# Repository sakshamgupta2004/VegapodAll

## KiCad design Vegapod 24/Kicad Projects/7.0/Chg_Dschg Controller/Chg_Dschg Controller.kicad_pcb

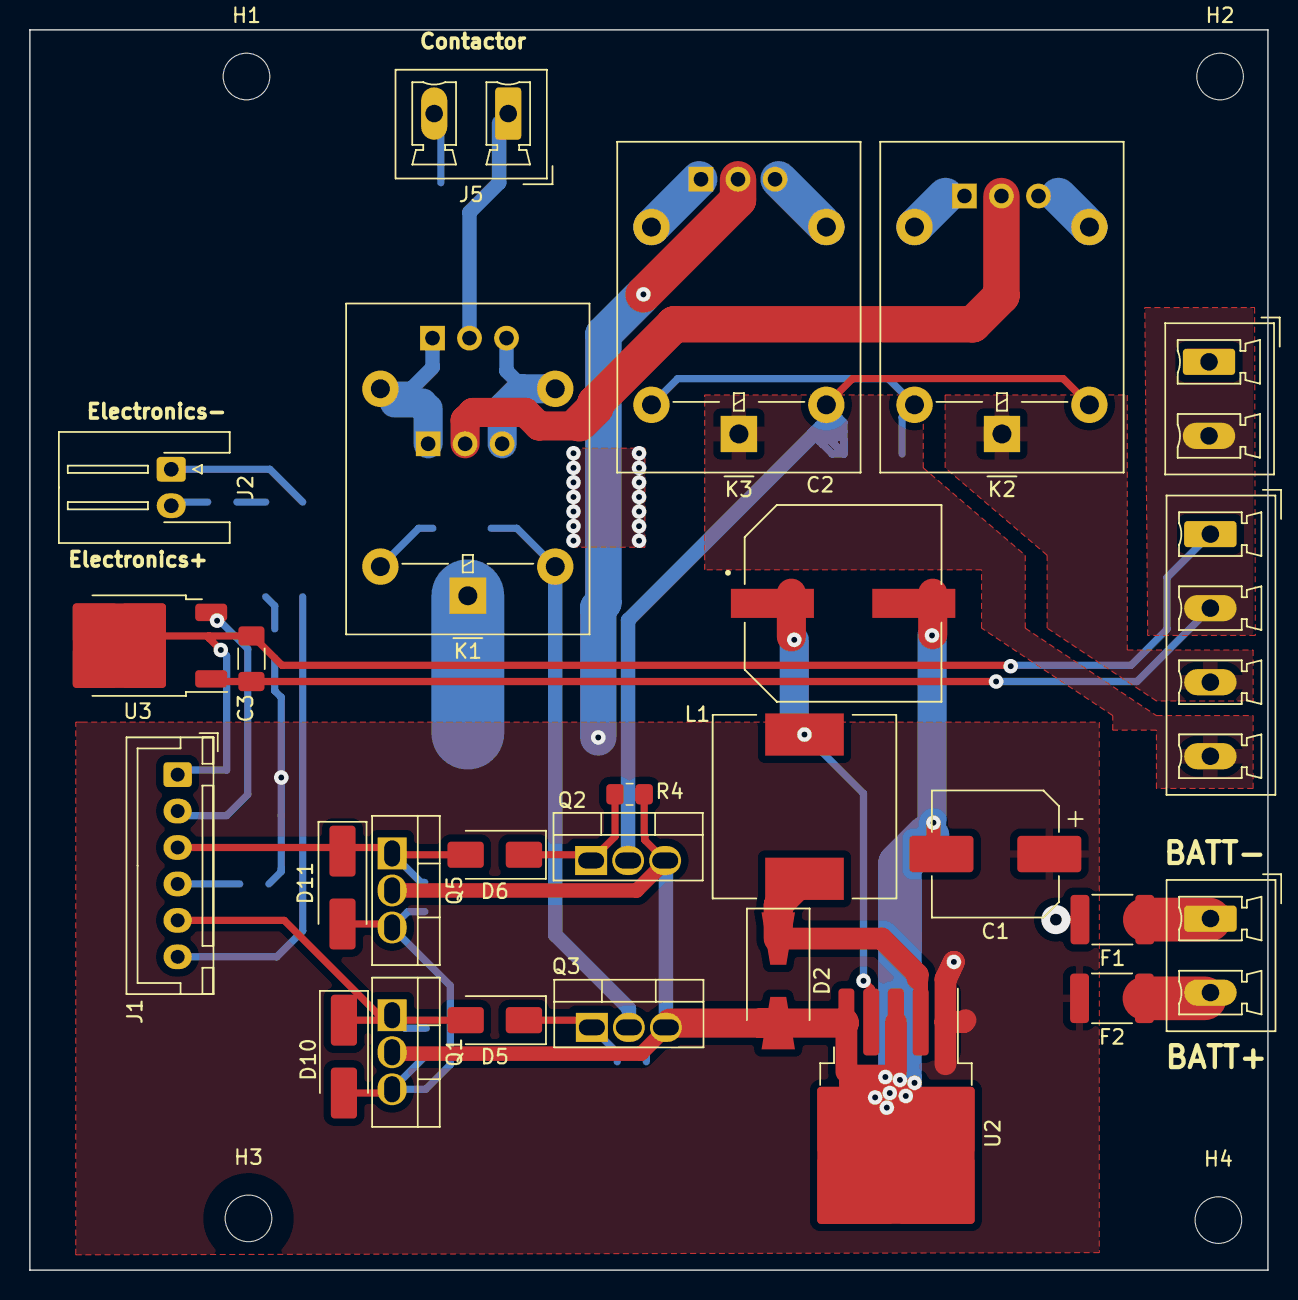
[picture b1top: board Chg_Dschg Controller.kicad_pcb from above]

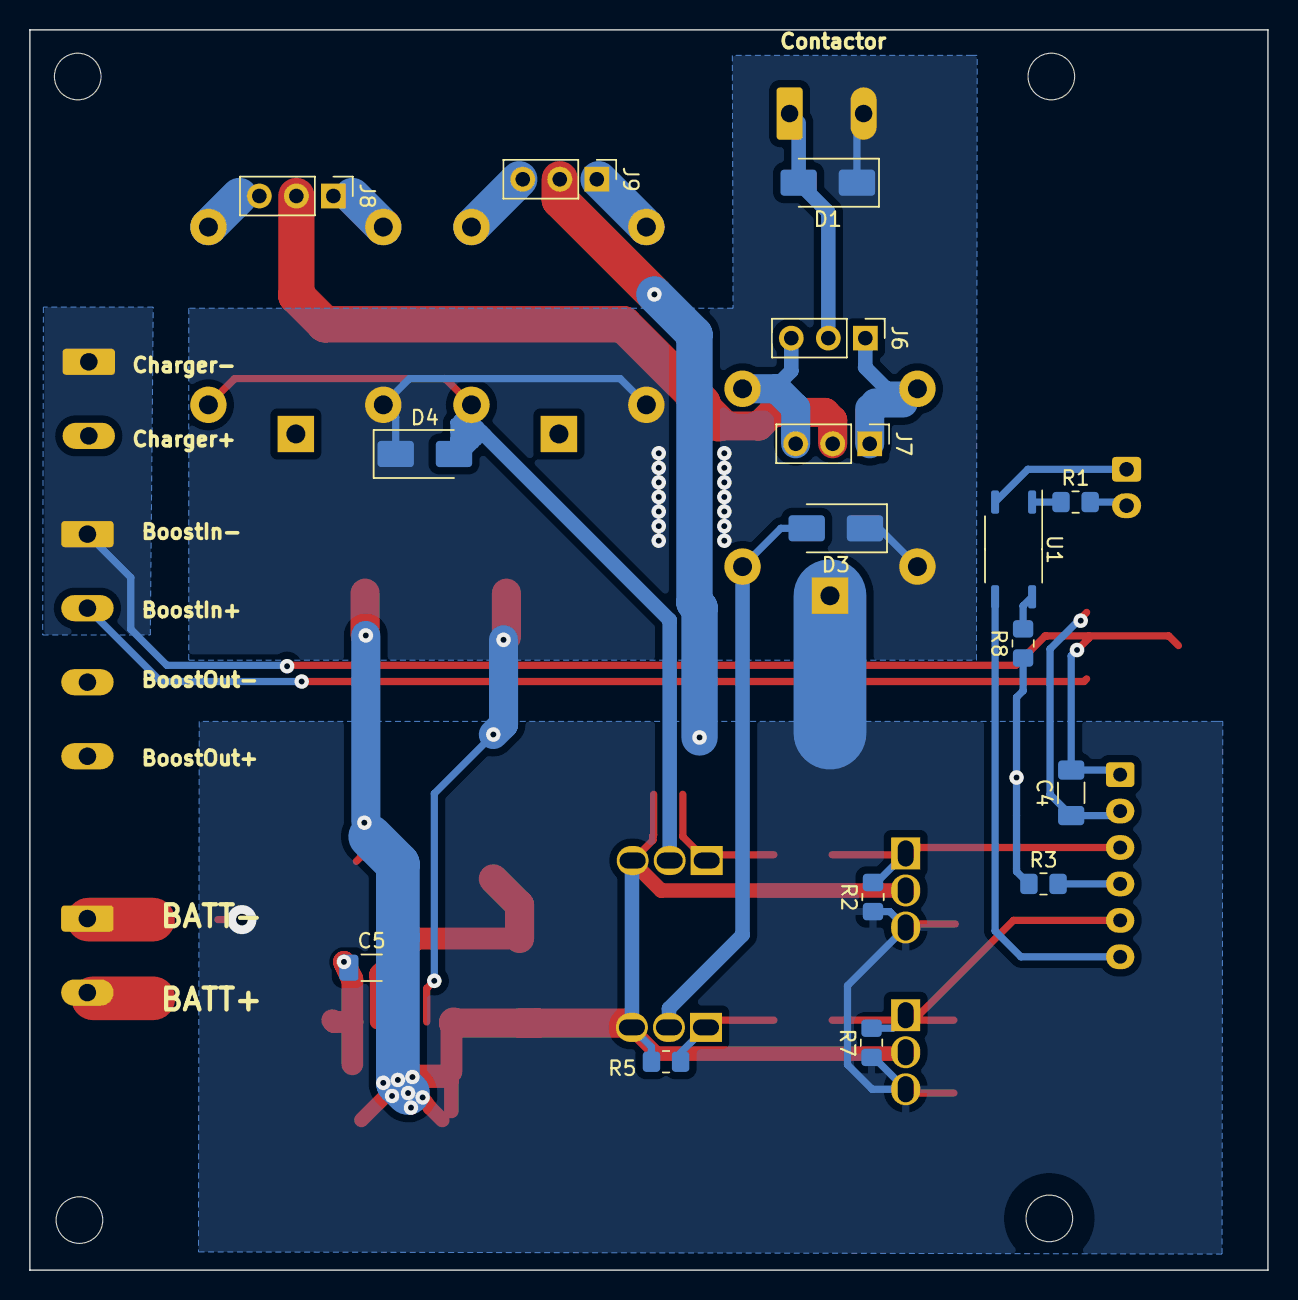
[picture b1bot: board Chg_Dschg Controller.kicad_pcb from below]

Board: 2 copper layers, 85.0 x 85.1 mm, 47 parts (16 on the bottom side), 32 nets.

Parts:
C1: 100uF 50V; CP_Elec_8x10.5
C2: 25V 1000uF; CAP_EEEFK1E102AQ
C3, C4, C5: 1uF; C_1206_3216Metric_Pad1.33x1.80mm_HandSolder
D1, D3, D4, D5, D6: 1n4007; D_SMA
D2: SS56; D_SMA-SMB_Universal_Handsoldering
D10, D11: D_Zener; D_SMA_Handsoldering
F1, F2: 5A 1808; R_1812_4532Metric_Pad1.30x3.40mm_HandSolder
H1, H2, H3, H4: MountingHole; MountingHole_3.2mm_M3
J1: Slave socket; JST_XH_B6B-XH-A_1x06_P2.50mm_Vertical
J2: Electronics; JST_XH_S2B-XH-A-1_1x02_P2.50mm_Horizontal
J3: Charger; PhoenixContact_MCV_1,5_2-G-5.08_1x02_P5.08mm_Vertical
J4: Battery; PhoenixContact_MCV_1,5_2-G-5.08_1x02_P5.08mm_Vertical
J5: Contactor; PhoenixContact_MCV_1,5_2-G-5.08_1x02_P5.08mm_Vertical
J6: NO/NC Contactor; PinHeader_1x03_P2.54mm_Vertical
J7: NC/NO Charge; PinHeader_1x03_P2.54mm_Vertical
J8: NO/NC Charge-; PinHeader_1x03_P2.54mm_Vertical
J9: NO/NC Charge+; PinHeader_1x03_P2.54mm_Vertical
J10: Conn_01x04_Pin; PhoenixContact_MCV_1,5_4-G-5.08_1x04_P5.08mm_Vertical
K1, K2, K3: Relay_SPDT; Relay_SPDT_Omron-G5LE-1
L1: CDRH127 100u; L_12x12mm_H8mm
Q1, Q2, Q3, Q5: IRLZ44N; TO-220-3_Vertical
R1: 470; R_0805_2012Metric_Pad1.20x1.40mm_HandSolder
R2, R3, R7, R8: 10k; R_0805_2012Metric_Pad1.20x1.40mm_HandSolder
R4, R5: 100k; R_0805_2012Metric_Pad1.20x1.40mm_HandSolder
U1: TLP185; SOIC-4_4.55x3.7mm_P2.54mm
U2: LM2576HVS-12; TO-263-5_TabPin3
U3: LM78M05_TO252; TO-252-2

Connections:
+BATT: C1.1, C5.1, F2.2, J9.2, R3.1, R8.1, U2.1 (VIN)
-BATT: D10.2 (A), D11.2 (A), F1.2, K1.1, Q1.3 (S), Q5.3 (S), R2.1, R7.1
/5V: C4.1, J1.2, U3.3 (VO)
/12V: C2.1, D1.1 (K), D3.1 (K), D4.1 (K), J5.2, K1.5, K2.5, K3.5, L1.2, U2.4 (FB)
/NCR1: J6.1, J7.1, K1.4
/NOR1: J6.3, J7.3, K1.3
BOOSTIN+: C3.1, J3.2, J10.2, U3.1 (VI)
BOOSTIN-: C3.2, C4.2, J1.1, J3.1, J10.1, U3.2 (GND)
BOOSTOUT+: J10.4, K3.1
BOOSTOUT-: J10.3, K2.1
unnamed: D1.2 (A), J5.1, J6.2
unnamed: C1.2, C2.2, C5.2, D2.2 (A), Q1.2 (D), Q2.3 (S), Q3.3 (S), Q5.2 (D), R4.1, R5.1, U2.3 (GND), U2.5 (~ON/OFF)
unnamed: D2.1 (K), L1.1, U2.2 (OUT)
unnamed: D3.2 (A), K1.2, Q3.2 (D)
unnamed: D4.2 (A), K2.2, K3.2, Q2.2 (D)
unnamed: D5.1 (K), Q3.1 (G), R5.2
unnamed: D6.1 (K), Q2.1 (G), R4.2
unnamed: D5.2 (A), D10.1 (K), J1.5, Q1.1 (G), R7.2
unnamed: D6.2 (A), D11.1 (K), J1.3, Q5.1 (G), R2.2
unnamed: J1.4, R3.2
unnamed: J1.6, U1.4
unnamed: J2.1, U1.3
unnamed: J2.2, R1.2
unnamed: F1.1, J4.1
unnamed: F2.1, J4.2
unnamed: J7.2, J8.2
unnamed: J8.1, K2.4
unnamed: J8.3, K2.3
unnamed: J9.1, K3.4
unnamed: J9.3, K3.3
unnamed: R1.1, U1.1
unnamed: R8.2, U1.6

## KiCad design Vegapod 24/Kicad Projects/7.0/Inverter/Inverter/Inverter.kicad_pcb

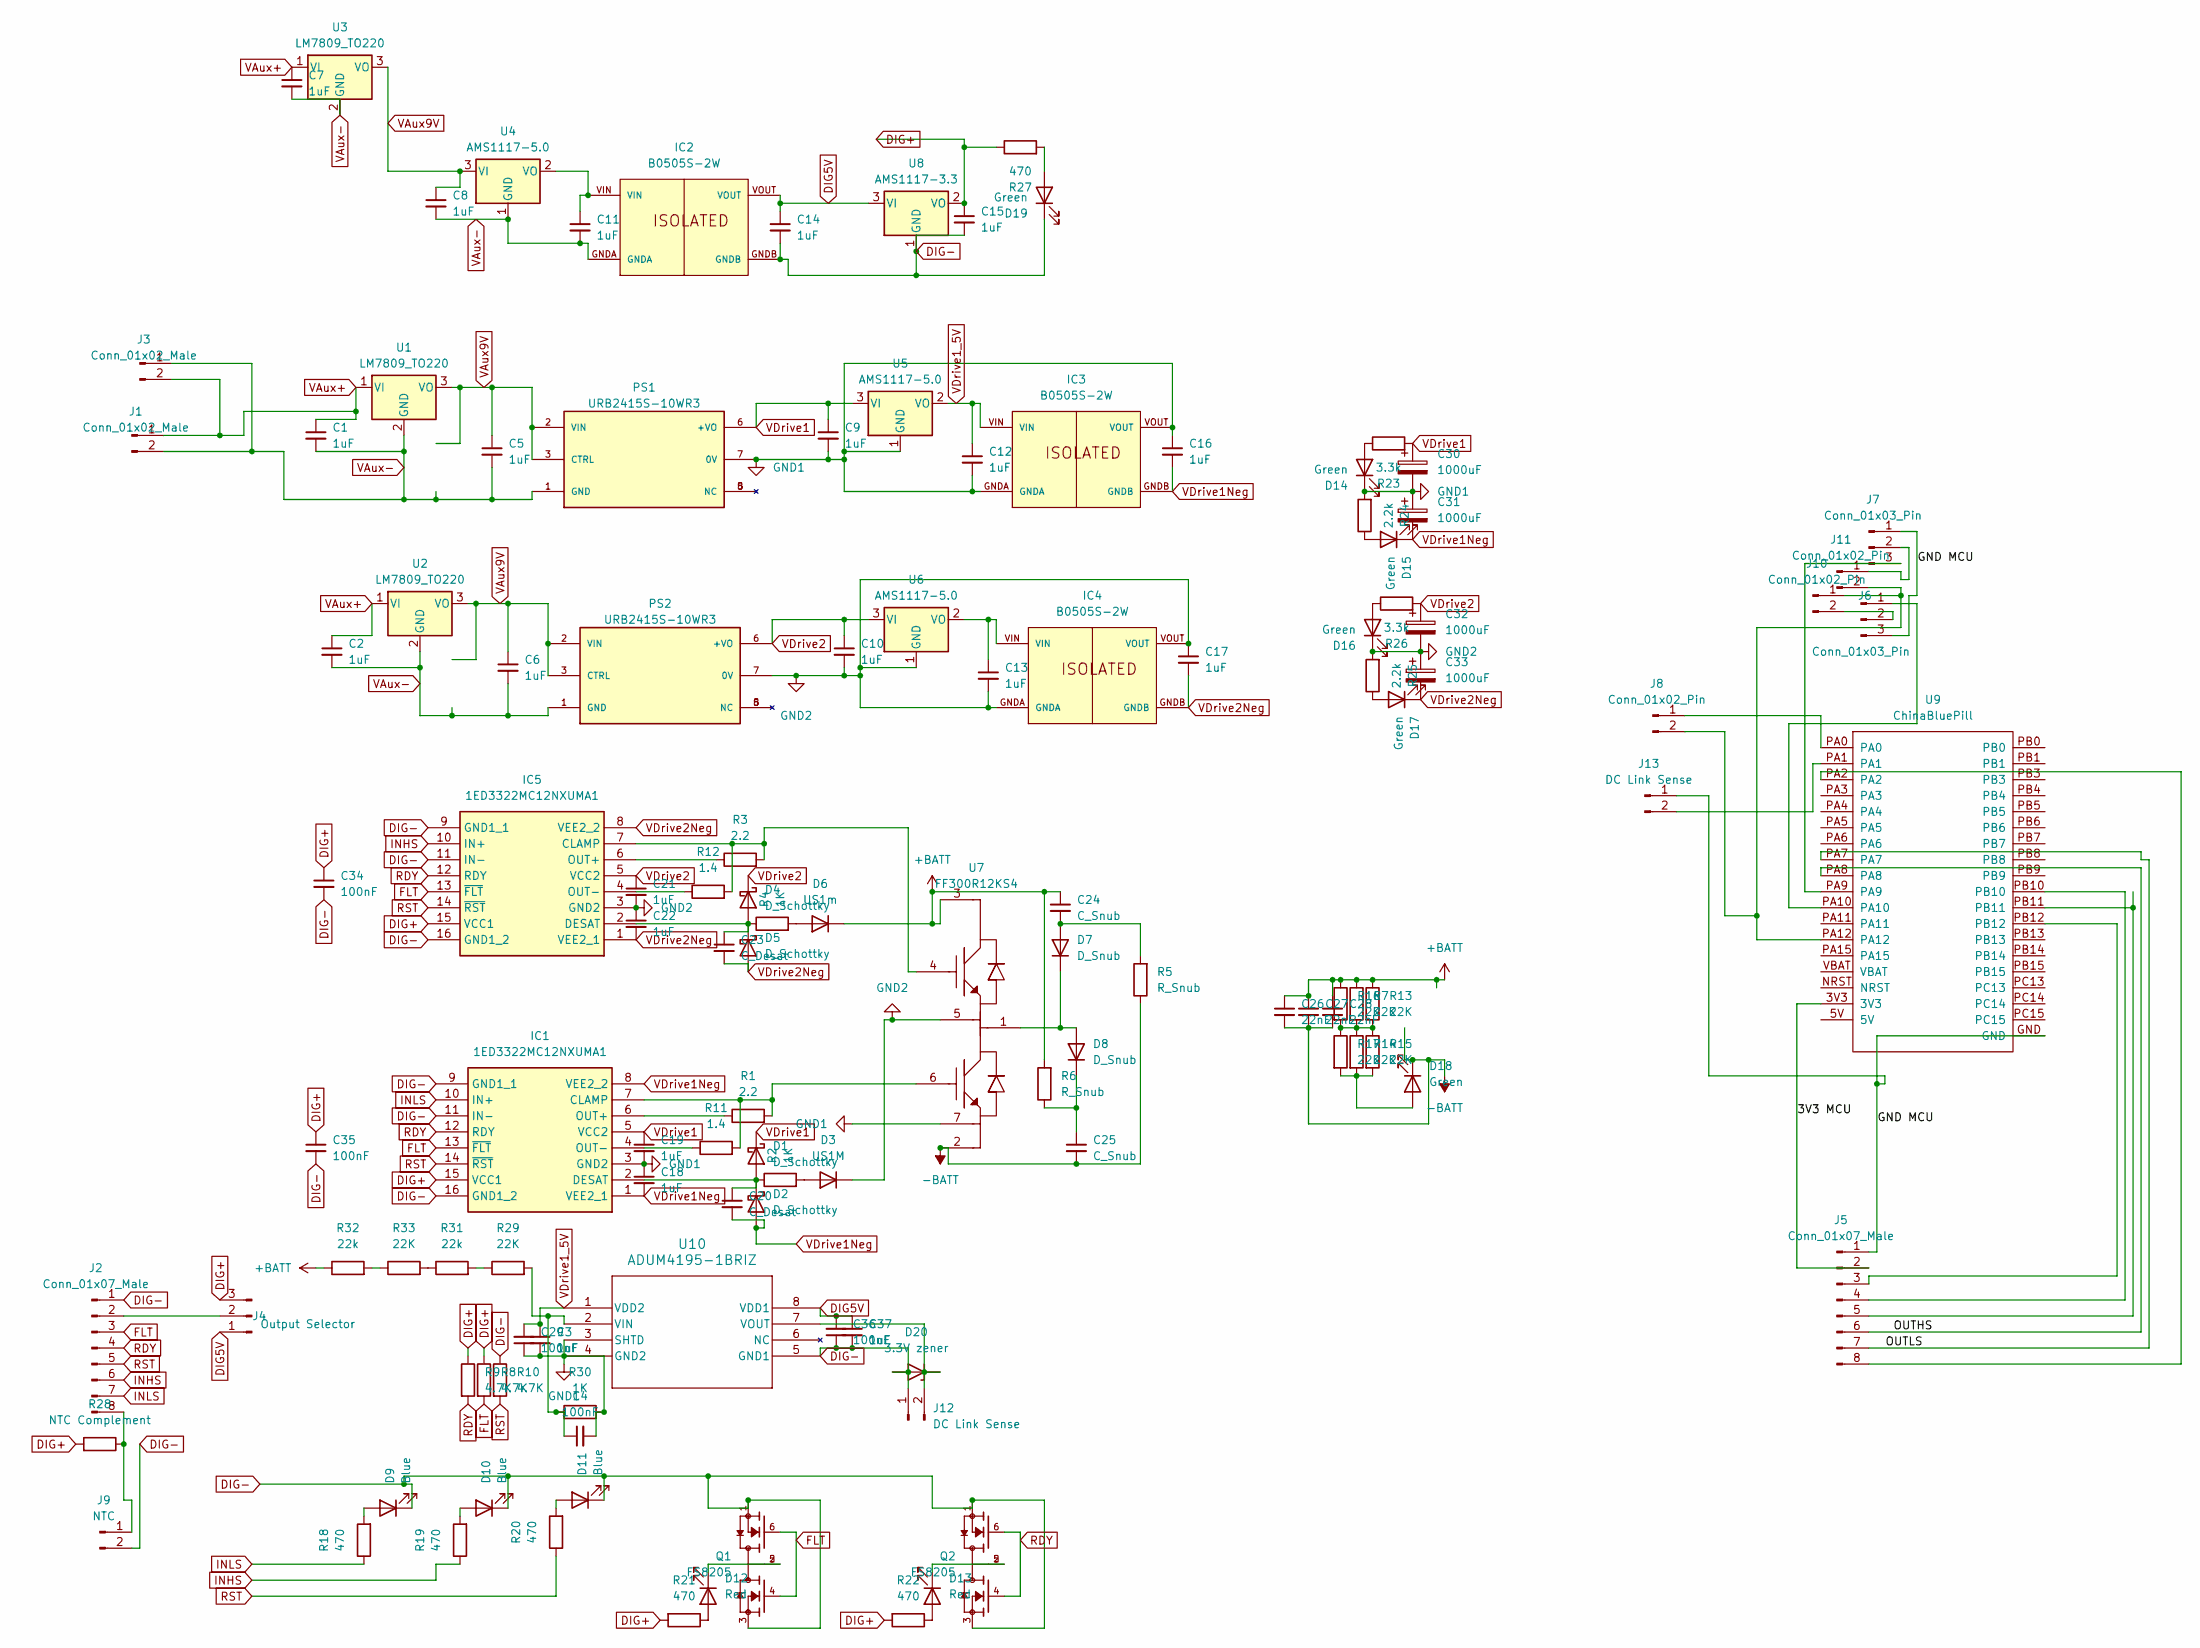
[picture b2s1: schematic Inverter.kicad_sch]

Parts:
C1, C2, C3, C5, C6, C7, C8, C9, C10, C11, C12, C13, C14, C15, C16, C17, C18, C19, C21, C22, C37: 1uF; C_1206_3216Metric_Pad1.33x1.80mm_HandSolder
C4, C29, C34, C35, C36: 100nF; C_0603_1608Metric_Pad1.08x0.95mm_HandSolder
C20, C23: C_Desat; C_0603_1608Metric_Pad1.08x0.95mm_HandSolder
C24, C25: C_Snub; C_Rect_L24.0mm_W8.3mm_P22.50mm_MKT
C26, C27, C28: 22nF; C_1206_3216Metric_Pad1.33x1.80mm_HandSolder
C30, C31, C32, C33: 1000uF; CAP_EEEFK1E102AQ
D1, D2, D4, D5: D_Schottky; D_SMA_Handsoldering
D3: US1M; D_SMA_Handsoldering
D6: US1m; D_SMA_Handsoldering
D7, D8: D_Snub; D_DO-201AE_P15.24mm_Horizontal
D9, D10, D11: Blue; LED_0805_2012Metric_Pad1.15x1.40mm_HandSolder
D12, D13: Red; LED_0805_2012Metric_Pad1.15x1.40mm_HandSolder
D14, D15, D16, D17, D18, D19: Green; LED_0805_2012Metric_Pad1.15x1.40mm_HandSolder
D20: 3.3V zener; D_MicroMELF_Handsoldering
IC1, IC5: 1ED3322MC12NXUMA1; SOIC127P1030X265-16N; Mouser Part Number 726-1ED3322MC12NXUMA
IC2, IC3, IC4: B0505S-2W; MPN B0505S-2W; DigiKey_Part_Number 2725-B0505S-2W-ND
J1, J3: Conn_01x02_Male; JST_XH_S2B-XH-A_1x02_P2.50mm_Horizontal
J2, J5: Conn_01x07_Male; JST_XH_B8B-XH-A_1x08_P2.50mm_Vertical
J4: Output Selector; PinSocket_1x03_P1.27mm_Vertical
J6, J7: Conn_01x03_Pin; JST_XH_S3B-XH-A_1x03_P2.50mm_Horizontal
J8, J10, J11: Conn_01x02_Pin; PinHeader_1x02_P1.27mm_Vertical
J9: NTC; PinHeader_1x02_P1.27mm_Vertical
J12, J13: DC Link Sense; PinHeader_1x02_P2.54mm_Vertical
PS1, PS2: URB2415S-10WR3; CONV_URB2415S-10WR3; PARTREV 2020.11.09-A/4; DigiKey_Part_Number 2725-URB2415S-10WR3-ND
Q1, Q2: FS8205; SOT95P280X145-6N; PARTREV 1.9
R1, R3: 2.2; R_0805_2012Metric_Pad1.20x1.40mm_HandSolder
R2, R4: 1K; R_0603_1608Metric_Pad0.98x0.95mm_HandSolder
R5, R6: R_Snub; R_Box_L26.0mm_W5.0mm_P20.00mm
R7, R13, R14, R15, R16, R17: 22K; R_1206_3216Metric_Pad1.30x1.75mm_HandSolder
R8, R9, R10: 4.7K; R_0805_2012Metric_Pad1.20x1.40mm_HandSolder
R11, R12: 1.4; R_0805_2012Metric_Pad1.20x1.40mm_HandSolder
R18, R19, R20, R21, R22, R27: 470; R_0603_1608Metric_Pad0.98x0.95mm_HandSolder
R23, R26: 3.3k; R_0603_1608Metric_Pad0.98x0.95mm_HandSolder
R24, R25: 2.2k; R_0603_1608Metric_Pad0.98x0.95mm_HandSolder
R28: NTC Complement; R_0805_2012Metric_Pad1.20x1.40mm_HandSolder
R29, R33: 22K; R_0805_2012Metric_Pad1.20x1.40mm_HandSolder
R30: 1K; R_0805_2012Metric_Pad1.20x1.40mm_HandSolder
R31, R32: 22k; R_0805_2012Metric_Pad1.20x1.40mm_HandSolder
U1, U2, U3: LM7809_TO220; TO-220-3_Vertical
U4, U5, U6: AMS1117-5.0; SOT-223-3_TabPin2
U7: FF300R12KS4
U8: AMS1117-3.3; SOT-223-3_TabPin2
U9: ChinaBluePill
U10: ADUM4195-1BRIZ; RI-8-1_ADI

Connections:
+BATT: C24.1, C26.1, C27.1, C28.1, D6.1 (K), R6.2, R7.1, R13.1, R16.1, R32.1, U7.3
-BATT: C25.2, C26.2, C27.2, C28.2, D18.1 (K), R5.1, U7.2
/3V3 MCU: J5.2, U9.3V3
/GND MCU: J5.1, J6.3, J7.1, J13.1, U9.GND
/OUTHS: J5.6, U9.PA8
/OUTLS: J5.7, U9.PA7
DIG5V: C14.1, C36.2, C37.1, IC2.VOUT, J4.1, U8.3 (VI), U10.8 (VDD1)
DIG+: C15.1, C34.1, C35.1, IC1.15 (VCC1), IC5.15 (VCC1), J4.3, R8.1, R9.1, R21.2, R22.2, R27.1, R28.2, U8.2 (VO)
DIG-: C14.2, C15.2, C34.2, C35.2, C36.1, C37.2, D9.1 (K), D10.1 (K), D11.1 (K), D19.1 (K), D20.2 (A), IC1.9 (GND1_1), IC1.11 (IN-), IC1.16 (GND1_2), IC2.GNDB, IC5.9 (GND1_1), IC5.11 (IN-), IC5.16 (GND1_2), J2.1, J9.2, J12.1, Q1.1, Q1.3, Q2.1, Q2.3, R10.1, U8.1 (GND), U10.5 (GND1)
FLT: IC1.13 (~FLT), IC5.13 (~FLT), J2.3, Q1.4, Q1.6, R8.2
GND1: C3.2, C4.2, C9.2, C12.2, C16.1, C18.1, C19.2, C29.1, C30.2, C31.1, D14.1 (K), IC1.3 (GND2), IC3.GNDA, IC3.VOUT, PS1.7 (0V), R24.2, R30.2, U5.1 (GND), U7.7, U10.3 (SHTD), U10.4 (GND2)
GND2: C10.2, C13.2, C17.1, C21.2, C22.1, C32.2, C33.1, D3.1 (K), D16.1 (K), IC4.GNDA, IC4.VOUT, IC5.3 (GND2), PS2.7 (0V), R25.2, U6.1 (GND), U7.5
INHS: IC5.10 (IN+), J2.6, R19.1
INLS: IC1.10 (IN+), J2.7, R18.1
unnamed: C20.1, D1.2 (A), D2.1 (K), IC1.2 (DESAT), R2.1
unnamed: D3.2 (A), R2.2
unnamed: C23.1, D4.2 (A), D5.1 (K), IC5.2 (DESAT), R4.1
unnamed: D6.2 (A), R4.2
unnamed: C24.2, D7.2 (A), R5.2
unnamed: D7.1 (K), D8.2 (A), U7.1
unnamed: C25.1, D8.1 (K), R6.1
unnamed: D9.2 (A), R18.2
unnamed: D10.2 (A), R19.2
unnamed: D11.2 (A), R20.2
unnamed: D12.2 (A), R21.1
unnamed: D12.1 (K), Q1.2, Q1.5
unnamed: D13.2 (A), R22.1
unnamed: D13.1 (K), Q2.2, Q2.5
unnamed: D14.2 (A), R23.1
unnamed: D15.2 (A), R24.1
unnamed: D16.2 (A), R26.1
unnamed: D17.2 (A), R25.1
unnamed: D18.2 (A), R14.2, R15.2, R17.2
unnamed: D19.2 (A), R27.2
unnamed: D20.1 (K), J12.2, U10.7 (VOUT)
unnamed: IC1.7 (CLAMP), R1.2, R11.2, U7.6
unnamed: IC1.6 (OUT+), R1.1
unnamed: IC1.4 (OUT-), R11.1
unnamed: IC5.7 (CLAMP), R3.2, R12.2, U7.4
unnamed: IC5.6 (OUT+), R3.1
unnamed: IC5.4 (OUT-), R12.1
unnamed: J2.2, J4.2
unnamed: J2.8, J9.1, R28.1
unnamed: J5.3, U9.PB12
unnamed: J5.4, U9.PB10
unnamed: J5.5, U9.PB11
unnamed: J5.8, U9.PA2
unnamed: J6.1, U9.PA10
unnamed: J7.3, U9.PA9
unnamed: J8.1, U9.PA0
unnamed: J8.2, J10.1, J11.2, U9.PA12
unnamed: J6.2, J10.2
unnamed: J7.2, J11.1
unnamed: J13.2, U9.PA1
unnamed: R7.2, R13.2, R14.1, R15.1, R16.2, R17.1
unnamed: R29.1, R31.2
unnamed: R31.1, R33.2
unnamed: R32.2, R33.1
unnamed: C11.1, IC2.VIN, U4.2 (VO)
unnamed: C13.1, IC4.VIN, U6.2 (VO)
unnamed: C4.1, R29.2, R30.1, U10.2 (VIN)
RDY: IC1.12 (RDY), IC5.12 (RDY), J2.4, Q2.4, Q2.6, R9.2
RST: IC1.14 (~RST), IC5.14 (~RST), J2.5, R10.2, R20.1
VAux+: C1.1, C2.1, C7.1, J1.1, J3.2, U1.1 (VI), U2.1 (VI), U3.1 (VI)
VAux-: C1.2, C2.2, C5.2, C6.2, C7.2, C8.2, C11.2, IC2.GNDA, J1.2, J3.1, PS1.1 (GND), PS2.1 (GND), U1.2 (GND), U2.2 (GND), U3.2 (GND), U4.1 (GND)
VDrive1: C9.1, C19.1, C30.1, D1.1 (K), IC1.5 (VCC2), PS1.6 (+VO), R23.2, U5.3 (VI)
VDrive1Neg: C16.2, C18.2, C20.2, C31.2, D2.2 (A), D15.1 (K), IC1.1 (VEE2_1), IC1.8 (VEE2_2), IC3.GNDB
VDrive1_5V: C3.1, C12.1, C29.2, IC3.VIN, U5.2 (VO), U10.1 (VDD2)
VDrive2: C10.1, C21.1, C32.1, D4.1 (K), IC5.5 (VCC2), PS2.6 (+VO), R26.2, U6.3 (VI)
VDrive2Neg: C17.2, C22.2, C23.2, C33.2, D5.2 (A), D17.1 (K), IC4.GNDB, IC5.1 (VEE2_1), IC5.8 (VEE2_2)

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
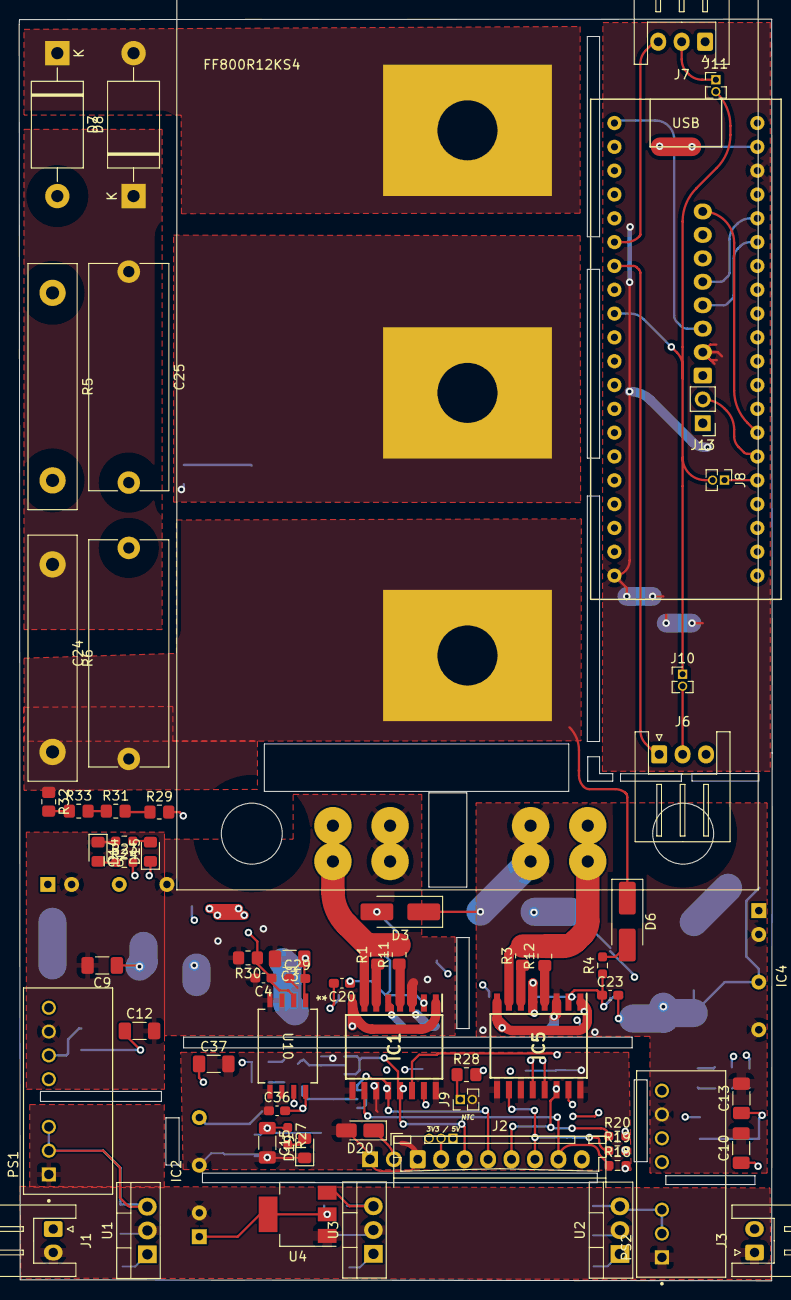
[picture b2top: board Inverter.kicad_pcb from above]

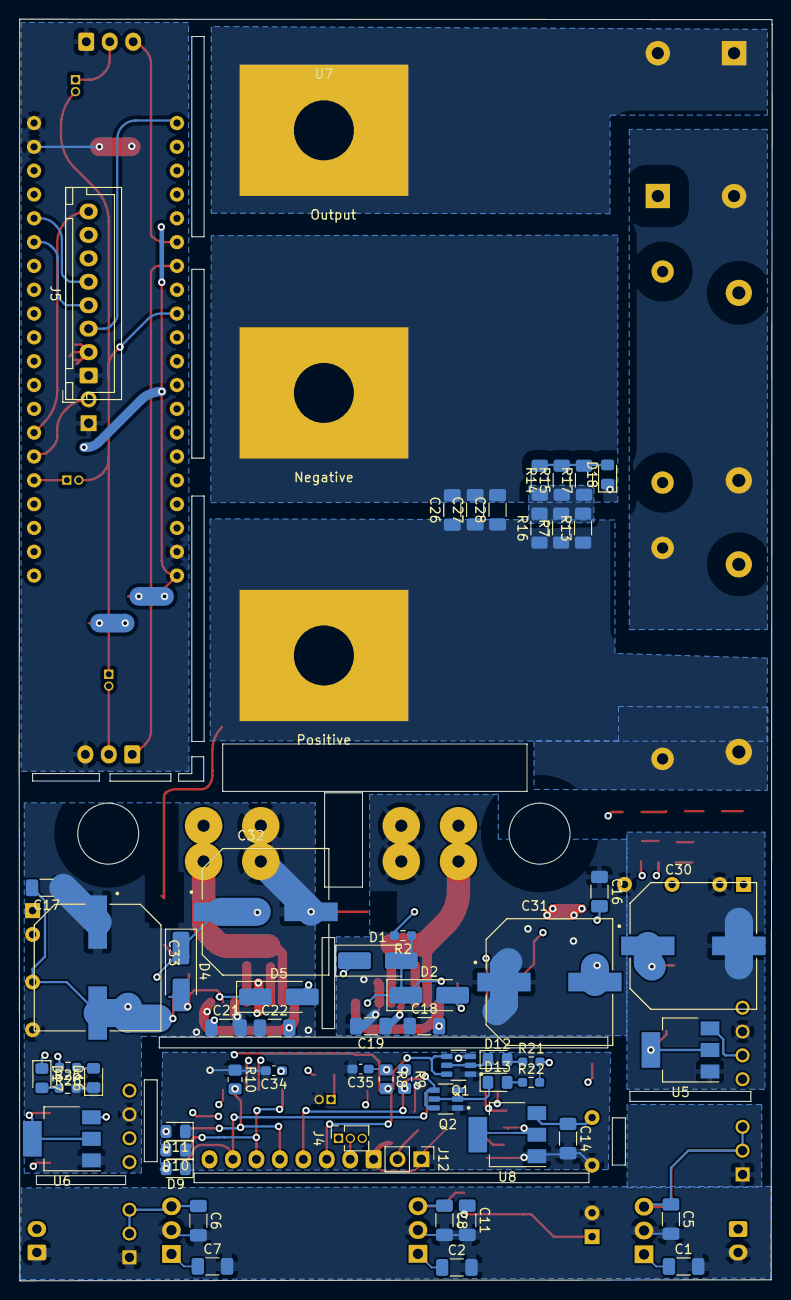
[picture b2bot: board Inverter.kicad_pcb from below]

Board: 4 copper layers, 80.3 x 134.5 mm, 122 parts (58 on the bottom side), 73 nets.

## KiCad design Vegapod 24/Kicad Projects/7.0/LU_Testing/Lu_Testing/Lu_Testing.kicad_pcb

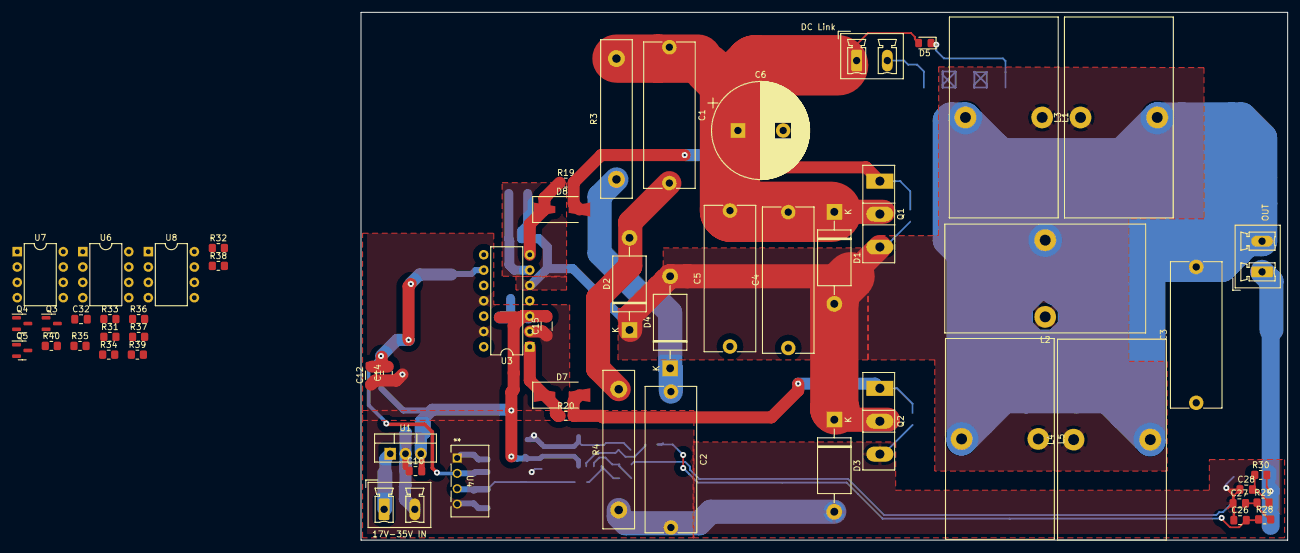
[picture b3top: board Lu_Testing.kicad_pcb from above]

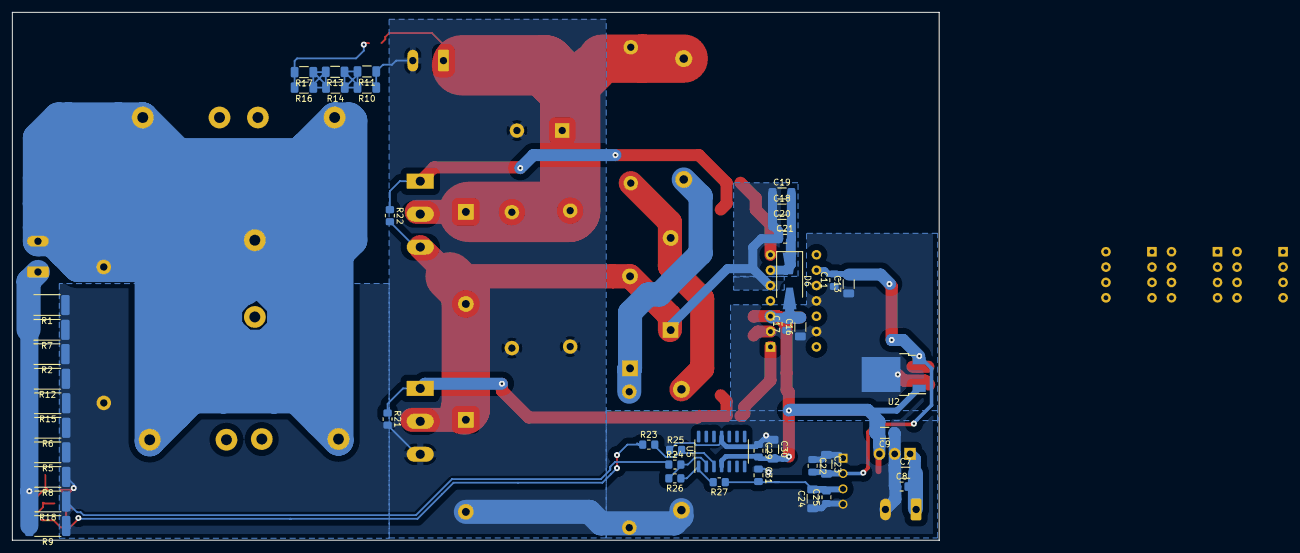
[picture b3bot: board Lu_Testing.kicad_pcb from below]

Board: 2 copper layers, 153.4 x 87.4 mm, 101 parts (44 on the bottom side), 34 nets.

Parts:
C1, C2: C_Snub; C_Rect_L24.0mm_W8.3mm_P22.50mm_MKT
C3, C4, C5: 1uF 400V; C_Rect_L24.0mm_W8.3mm_P22.50mm_MKT
C6: 56uF; CP_Radial_D16.0mm_P7.50mm
C7, C9, C12, C13, C15, C16, C18, C19, C20, C23, C24, C30: 10u; C_1206_3216Metric_Pad1.33x1.80mm_HandSolder
C8, C10, C11, C14, C17, C21, C22, C25, C29, C31: 100n; C_0805_2012Metric_Pad1.18x1.45mm_HandSolder
C26, C27, C28, C32: 47n; C_0805_2012Metric_Pad1.18x1.45mm_HandSolder
D1, D2, D3, D4: MUR460; D_DO-201AE_P15.24mm_Horizontal
D5: LED; D_0805_2012Metric_Pad1.15x1.40mm_HandSolder
D6, D7, D8: US1M; D_SMA-SMB_Universal_Handsoldering
J1: DC Link; PhoenixContact_MCV_1,5_2-G-5.08_1x02_P5.08mm_Vertical
J2: OUT; PhoenixContact_MCV_1,5_2-G-5.08_1x02_P5.08mm_Vertical
J3: 17V-35V IN; PhoenixContact_MCV_1,5_2-G-5.08_1x02_P5.08mm_Vertical
L1, L2, L3, L4, L5: 330uH 5.2A; L_Toroid_Vertical_L33.0mm_W17.8mm_P12.70mm_Pulse_KM-5
Q1, Q2: Q_NMOS_GDS; TO-247-3_Vertical
Q3, Q4, Q5: Q_PMOS_GSD; SOT-23
R1, R2, R5, R6, R7, R8, R9, R12, R15, R18: 0.1Ohm 3W; R_2512_6332Metric_Pad1.40x3.35mm_HandSolder
R3, R4: R_Snub; R_Box_L26.0mm_W5.0mm_P20.00mm
R10, R11, R13, R14, R16, R17: 22K; R_1206_3216Metric_Pad1.30x1.75mm_HandSolder
R19, R20: 10; R_0805_2012Metric_Pad1.20x1.40mm_HandSolder
R21, R22: 1K; R_0805_2012Metric_Pad1.20x1.40mm_HandSolder
R23, R24, R25, R26, R38: 10k; R_0805_2012Metric_Pad1.20x1.40mm_HandSolder
R27, R31, R32, R33, R34, R35, R36, R40: 470; R_0805_2012Metric_Pad1.20x1.40mm_HandSolder
R28, R29, R30, R37: 220; R_0805_2012Metric_Pad1.20x1.40mm_HandSolder
R39: 1k; R_0805_2012Metric_Pad1.20x1.40mm_HandSolder
U1: LM7815_TO220; TO-220-3_Vertical
U2: KA78M05_TO252; TO-252-2
U3: IR2110; DIP-14_W7.62mm
U4: B0505S-1WR3; B0505S_MNS
U5: LM324; SOIC-14_3.9x8.7mm_P1.27mm
U6, U7, U8: 6N137; DIP-8_W7.62mm

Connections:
+5V: C11.2, C12.2, C13.2, C14.2, C22.2, C23.2, Q3.2 (S), Q4.2 (S), Q5.2 (S), R31.1, R32.1, R33.1, U2.3 (VO), U3.9 (VDD), U4.2 (VIN), U6.7 (EN), U6.8 (VCC), U7.7 (EN), U7.8 (VCC), U8.7 (EN), U8.8 (VCC)
+15V: C9.2, C10.2, C15.2, C16.2, C17.2, C29.2, C30.2, D6.2 (A), U1.3 (VO), U2.1 (VI), U3.3 (VCC), U5.4 (V+)
-5V: C24.2, C25.2, C31.2, R27.1, U4.3 (0V)
A0: R38.2, R39.1, R40.2
DC Link+: C1.1, C4.2, C5.2, C6.1, D1.1 (K), D5.2 (A), J1.1, Q1.2 (D), R3.2
DC Link-: C2.2, C3.1, C4.1, C5.1, C6.2, C7.1, C8.1, C9.1, C10.1, C11.1, C12.1, C13.1, C14.1, C15.1, C16.1, C17.1, C22.1, C23.1, C24.1, C25.1, C26.1, C27.1, C28.1, C29.1, C30.1, C31.1, C32.1, D3.2 (A), J1.2, J3.2, Q2.3 (S), R1.1, R2.1, R4.1, R5.1, R6.1, R7.1, R8.1, R9.1, R10.1, R11.1, R12.1, R15.1, R18.1, R21.2, R24.1, R25.1, R34.2, R35.2, R36.2, R40.1, U1.2 (GND), U2.2 (GND), U3.2 (COM), U3.11 (SD), U3.13 (VSS), U4.1 (GND), U4.4 (+VO), U5.11 (V-), U6.5 (GND), U7.5 (GND), U8.5 (GND)
HIN: Q4.3 (D), R35.1, U3.10 (HIN)
LIN: Q5.3 (D), R36.1, U3.12 (LIN)
unnamed: C1.2, D2.2 (A), R4.2
unnamed: C2.1, D4.1 (K), R3.1
unnamed: C3.2, J2.2, L1.2, L2.2, L3.2, L4.2, L5.2
unnamed: C7.2, C8.2, J3.1, U1.1 (VI)
unnamed: C18.2, C19.2, C20.2, C21.2, D6.1 (K), U3.6 (VB)
unnamed: C26.2, R23.1, R28.1
unnamed: C27.2, R28.2, R29.1
unnamed: C28.2, R29.2, R30.1
unnamed: D5.1 (K), R16.2, R17.2
unnamed: D7.1 (K), R20.1, U3.1 (LO)
unnamed: D7.2 (A), Q2.1 (G), R20.2, R21.1
unnamed: D8.1 (K), R19.1, U3.7 (HO)
unnamed: D8.2 (A), Q1.1 (G), R19.2, R22.1
unnamed: J2.1, R1.2, R2.2, R5.2, R6.2, R7.2, R8.2, R9.2, R12.2, R15.2, R18.2, R30.2
unnamed: Q3.1 (G), R31.2, U6.6 (VO)
unnamed: Q3.3 (D), R34.1, R37.2
unnamed: Q4.1 (G), R32.2, U7.6 (VO)
unnamed: Q5.1 (G), R33.2, U8.6 (VO)
unnamed: R10.2, R11.2, R13.1, R14.1
unnamed: R13.2, R14.2, R16.1, R17.1
unnamed: R23.2, R25.2, U5.3 (+)
unnamed: R24.2, R26.2, U5.2 (-)
unnamed: R26.1, R27.2, R39.2, U5.1
unnamed: R38.1, U5.5 (+)
unnamed: C32.2, R37.1, U5.6 (-)
VS: C18.1, C19.1, C20.1, C21.1, D1.2 (A), D2.1 (K), D3.1 (K), D4.2 (A), L1.1, L2.1, L3.1, L4.1, L5.1, Q1.3 (S), Q2.2 (D), R22.2, U3.5 (VS)
